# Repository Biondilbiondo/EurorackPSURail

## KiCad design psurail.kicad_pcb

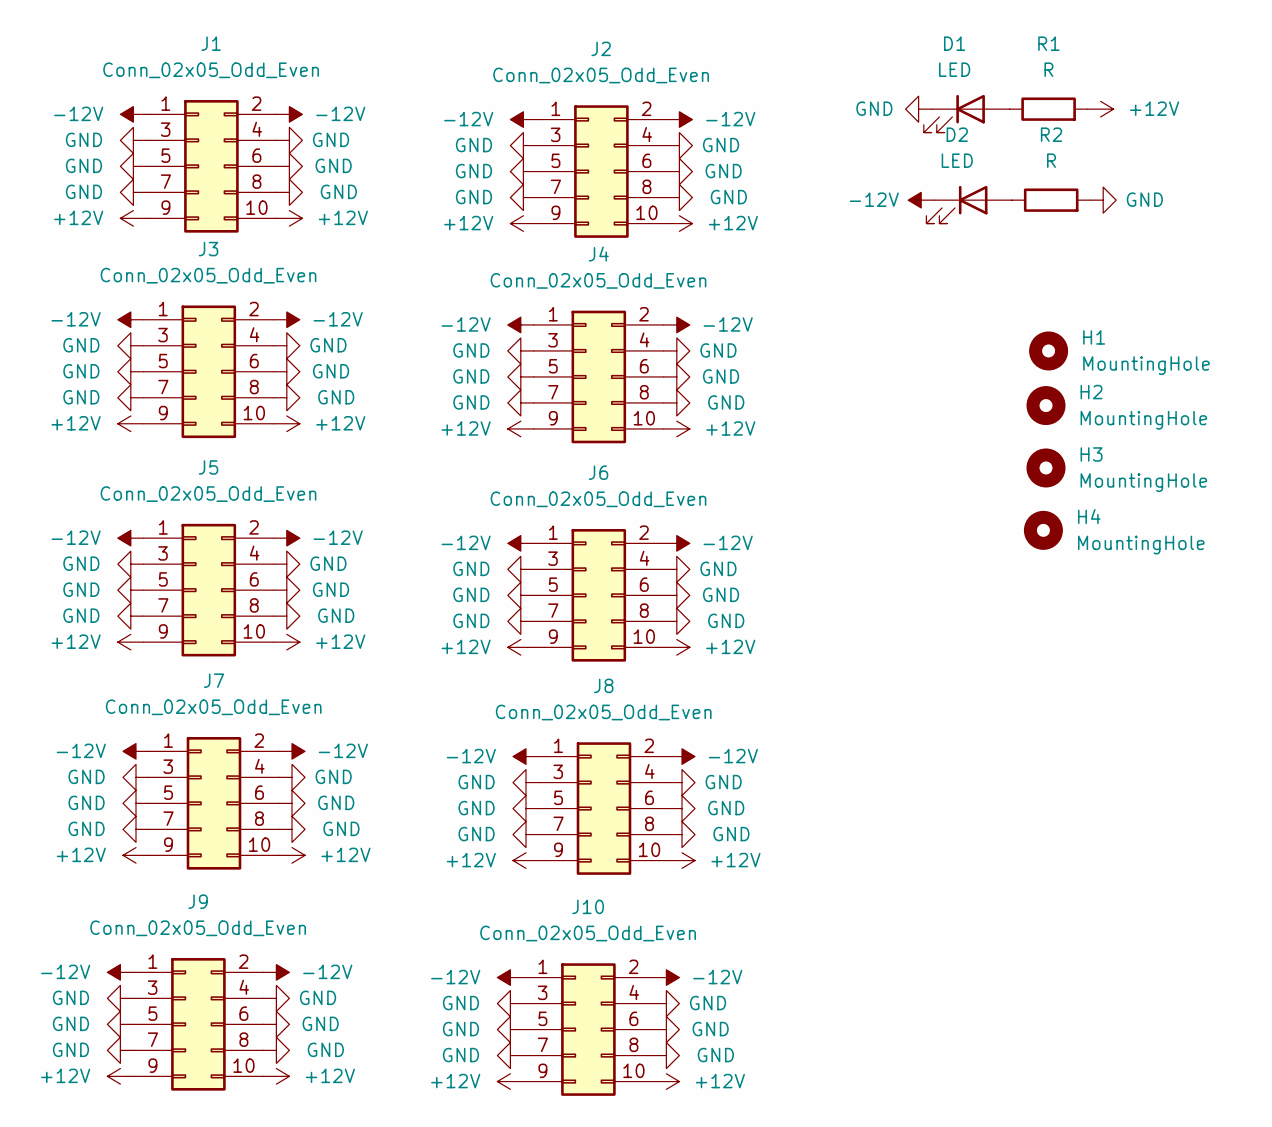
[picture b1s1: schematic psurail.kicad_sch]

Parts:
D1, D2: LED; LED_D3.0mm
H1, H2, H3: MountingHole; MountingHole_4mm
H4: MountingHole; IDC-Header_2x05_P2.54mm_Vertical
J1, J2, J3, J4, J5, J6, J7, J8, J9, J10: Conn_02x05_Odd_Even; IDC-Header_2x05_P2.54mm_Vertical
R1, R2: R; R_Axial_DIN0207_L6.3mm_D2.5mm_P2.54mm_Vertical

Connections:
+12V: J1.9, J1.10, J2.9, J2.10, J3.9, J3.10, J4.9, J4.10, J5.9, J5.10, J6.9, J6.10, J7.9, J7.10, J8.9, J8.10, J9.9, J9.10, J10.9, J10.10, R1.2
-12V: D2.1 (K), J1.1, J1.2, J2.1, J2.2, J3.1, J3.2, J4.1, J4.2, J5.1, J5.2, J6.1, J6.2, J7.1, J7.2, J8.1, J8.2, J9.1, J9.2, J10.1, J10.2
GND: D1.1 (K), J1.3, J1.4, J1.5, J1.6, J1.7, J1.8, J2.3, J2.4, J2.5, J2.6, J2.7, J2.8, J3.3, J3.4, J3.5, J3.6, J3.7, J3.8, J4.3, J4.4, J4.5, J4.6, J4.7, J4.8, J5.3, J5.4, J5.5, J5.6, J5.7, J5.8, J6.3, J6.4, J6.5, J6.6, J6.7, J6.8, J7.3, J7.4, J7.5, J7.6, J7.7, J7.8, J8.3, J8.4, J8.5, J8.6, J8.7, J8.8, J9.3, J9.4, J9.5, J9.6, J9.7, J9.8, J10.3, J10.4, J10.5, J10.6, J10.7, J10.8, R2.2
unnamed: D1.2 (A), R1.1
unnamed: D2.2 (A), R2.1

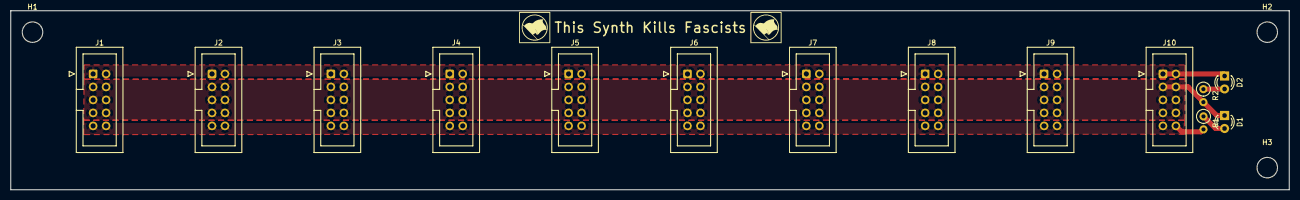
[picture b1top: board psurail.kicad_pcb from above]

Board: 2 copper layers, 250.0 x 35.0 mm, 17 parts (0 on the bottom side), 5 nets.

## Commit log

2025-11-21 First version, just leds and connections with 10 PSU headers
2025-11-21 Updated footprint for headers
2025-11-21 Added production files
